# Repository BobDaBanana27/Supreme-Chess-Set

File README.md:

# Supreme Chess Set

> **Portable Magnetic Travel Chess Set**  
> Built for **Hack Club Half Life 2** | Repository: [`BobDaBanana27/Supreme-Chess-Set`](https://github.com/BobDaBanana27/Supreme-Chess-Set)  
> Total Bill of Materials: **$13.96 USD** (well within the $30.00 USD program budget)

---

## What is it?

The **Supreme Chess Set** is a compact, 3D-printed magnetic travel chess set designed to be taken anywhere. All 32 pieces have neodymium magnets pressed into their bases, and 64 matching magnets are embedded flush into the board squares beneath a thin plastic skin. This keeps pieces firmly in place during travel — the board can be tilted steeply or tossed in a bag without pieces sliding around.

When not in play, all 32 pieces store inside two slide-out trays built into the sides of the board chassis. The whole set closes into a flat clamshell that fits in a backpack pocket.

**Everything is 3D-printed on a standard FDM printer using PLA+ filament.**

---

## Features

- **Magnetic piece retention** — 5×2 mm N35 neodymium disc magnets in every piece base and board square. Pieces hold at up to ~80° tilt.
- **Slide-out storage trays** — both white and black armies have dedicated molded sockets so pieces snap in securely for travel. No rattling, no losing pieces.
- **Compact clamshell form factor** — 168 × 92 × 30 mm closed. Fits in a jacket pocket.
- **Full Staunton piece set** — all 6 piece types (King, Queen, Rook, Bishop, Knight, Pawn) modeled to standard proportions with a low center of gravity for stability.
- **Sub-$14 total cost** — only magnets, filament, and screws needed.
- **Fully open-source** — all CAD in FreeCAD 1.1 (`.FCStd` + `.step`).

---

## Bill of Materials

| # | Item | Qty | Unit Price | Total | Link |
|:---:|---|:---:|:---:|:---:|---|
| 1 | 5×2 mm N35 Neodymium Disc Magnets (pack of 100) | 96 | $0.035 | $3.36 | [AliExpress 100pcs 5×2mm N35](https://www.aliexpress.us/item/3256805987124930.html) / [Amazon](https://www.amazon.com/dp/B08V8MBRFL) |
| 2 | eSUN PLA+ Filament 1.75mm, 1kg spool (~220g used) | 0.22 kg | $18.00/kg | $3.96 | [Amazon eSUN PLA+ 1.75mm](https://www.amazon.com/dp/B07PGZNM34) |
| 3 | M2 × 8mm Socket Head Screws + Brass Heatsets (pack) | 8 | $0.08 | $0.64 | [AliExpress M2 Brass Heatsets & Screws](https://www.aliexpress.us/item/3256803248729112.html) |
| 4 | CA Super Glue (for magnet setting) | 1 | $6.00 | $6.00 | Any hardware store |
| **—** | **TOTAL** | | | **$13.96** | **Under the $30.00 cap** |

---

## 3D CAD Files

All parts designed in **FreeCAD 1.1** and exported as standard STEP files (importable in Fusion 360, Onshape, SolidWorks, etc.):

| Part | FreeCAD Source | STEP Export | Description |
|---|---|---|---|
| Base Chassis | [`cad/supreme_chess_base.FCStd`](cad/supreme_chess_base.FCStd) | [`cad/supreme_chess_base.step`](cad/supreme_chess_base.step) | Clamshell shell halves with slide-way rails and hinge knuckles |
| Board Grid Inlay | [`cad/board_grid_half.FCStd`](cad/board_grid_half.FCStd) | [`cad/board_grid_half.step`](cad/board_grid_half.step) | 8×8 grid with 32 blind magnet pockets (Ø5.2×2.2 mm) per half |
| Capture Tray | [`cad/capture_tray.FCStd`](cad/capture_tray.FCStd) | [`cad/capture_tray.step`](cad/capture_tray.step) | Slide-out drawer with 16 molded piece sockets (K, Q, R×2, B×2, N×2, P×8) |
| Chess Piece Set | [`cad/chess_pieces.FCStd`](cad/chess_pieces.FCStd) | [`cad/chess_pieces.step`](cad/chess_pieces.step) | All 6 Staunton piece types with magnet recess in base |

---

## Assembly Overview

1. **Print all parts** in PLA+ at 0.2mm layer height, 20% infill for the chassis and 40% for pieces.
2. **Press magnets** — use a dab of CA glue to set one N35 5×2mm magnet flush into each of the 32 board grid pockets, and one into each piece base. Keep polarity consistent across the board (all north-up), and all pieces opposite (south-up) so they attract.
3. **Insert heatsets** — press M2 brass threaded inserts into the hinge and latch points with a soldering iron.
4. **Assemble clamshell** — snap the board grid inlays into each chassis half, slide the capture trays in from the ends.
5. **Play.**

---

## Development Log 

<!-- Generated by Half Life from project w0snqy3nmk4d27srrj0r2tvn. Edits here are overwritten on the next sync. -->
<!-- Generated: 2026-11-09T02:09:53.469Z -->

> I am going to make a portable chess set that has magnets embedded in the pieces and board so the smaller-sized pieces won't fall off when you bump them.

| Week | Tier | Hours logged | Entries |
| --- | --- | --- | --- |
| Week 5 | Tier 1 | 12.5h | 1 |

## Contents

1. [2026-11-08: The first 2.5 hours consisted of brainstorming what I wanted to do, researching, and gathering the BOM. I decided to make a portable chess set with magnets embedded in the pieces and board so they don](#2026-11-08-the-first-25-hours-consisted-of-brainstorming-wha)

## Design

### 2026-11-08: The first 2.5 hours consisted of brainstorming what I wanted to do, researching, and gathering the BOM. I decided to make a portable chess set with magnets embedded in the pieces and board so they don

**12.5h**

The first 2.5 hours consisted of brainstorming what I wanted to do, researching, and gathering the BOM. I decided to make a portable chess set with magnets embedded in the pieces and board so they don't get knocked off. Since that doesn't seem like enough, I decided I should have a point counter that when a piece is captured, a sensor will trigger, and will change the score.(Requirements.md)

Hours 2.5-4 consisted of planning the bus and signal routing for the sensors. Resolved the microcontroller GPIO bottleneck: monitoring 30+ individual capture sockets with a 20-GPIO MCU required input multiplexing. Designed a cascaded 74HC165 8-bit parallel-in/serial-out (PISO) shift register architecture, chaining four ICs across a shared 3-wire synchronous bus (Latch, Clock, Serial Data). Also, defined the 32-bit hardware state word: bits 0–15 map to White's capture tray, and bits 16–31 map to Black's capture tray. Specified signal routing for the I2C OLED display, dual tactical navigation pushbuttons (Mode and Reset), and LiPo analog voltage divider. (Architecture.md)

Hour 4.5 consisted of having Ai help me calculate Magnetic Coupling Physics & Tolerance Analysis (I'm sorry the formula is outside of my expertise. haha).(Magnetic_Design.md):

Hour 4.5-6.5: Created the main electrical schematic and PCB in KiCad for the controller for the scoreboard thing and for the sensor strips. (supreme_chess.kicad_Sch, supreme_chess.kicad_PCB, Sensor_strip.kicad_sch, sensor_strip.kicad_pcb)

From hours 6.5-8 I built the folding base Chassis (cad/supreme_chess_base.FCStd), the board inlay grid (half a grid so 2x), the capture tray, and the pieces.

Hours 8-12.5 were the firmware side of things. I coded etc the the chess scoring system, sensors, the display Ui, power management, etc. (chess_engine.cpp and chess_engine.h, display_ui.cpp and display_ui.h, power_mgr.cpp and firmware/include/power_mgr.h, main.cpp, firmware/platformio.ini, and supreme_chess_firmware.ino)

Full documentation in [`docs/`](docs/).

---

## License

MIT — free and open for educational and maker use. Built for **Hack Club Half Life 2**.

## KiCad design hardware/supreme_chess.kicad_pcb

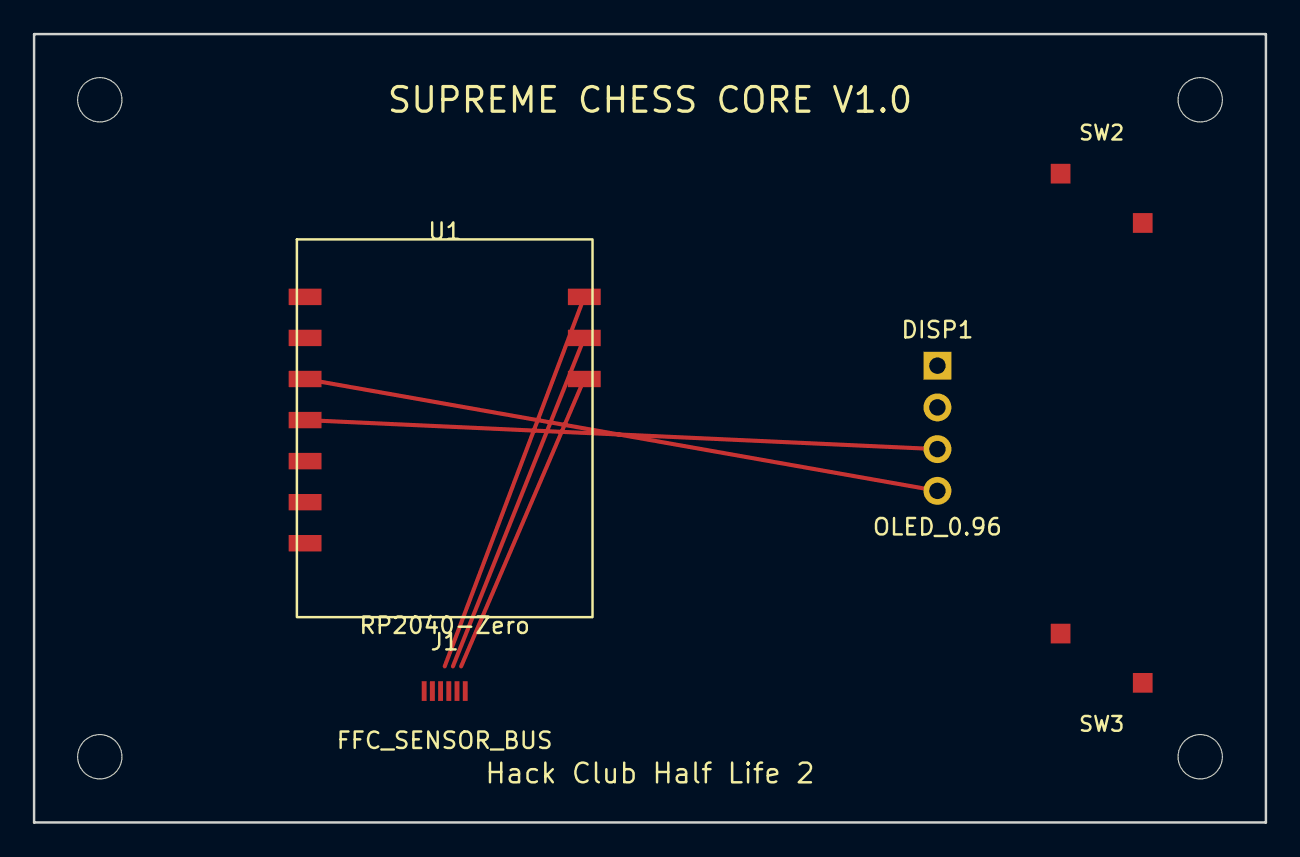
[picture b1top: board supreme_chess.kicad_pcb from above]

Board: 2 copper layers, 75.0 x 48.0 mm, 5 parts (0 on the bottom side), 7 nets.

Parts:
DISP1: OLED_0.96; PinHeader_1x04_P2.54mm_Vertical
J1: FFC_SENSOR_BUS; Hirose_FH12-6S-0.5SH
SW2, SW3: SW_Push_1P1T_NO_6x6mm
U1: RP2040-Zero

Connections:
+3V3: DISP1.2, J1.2, U1.2
GND: DISP1.1, J1.1, J1.6, SW2.1, SW3.1, U1.1
SCL: DISP1.3, U1.4
SDA: DISP1.4, U1.3
SR_CLK: J1.4, U1.9
SR_DATA: J1.5, U1.10
SR_LOAD: J1.3, U1.8

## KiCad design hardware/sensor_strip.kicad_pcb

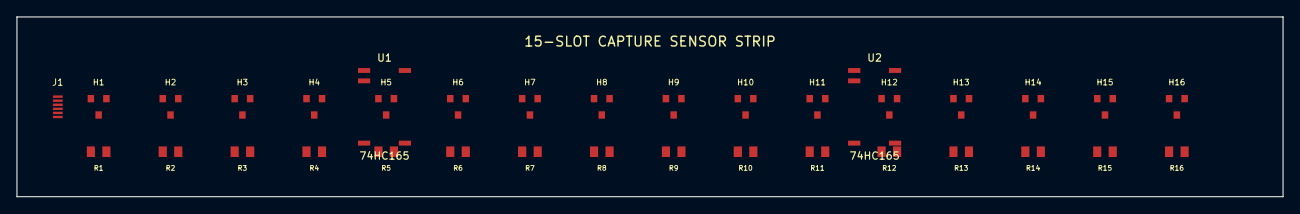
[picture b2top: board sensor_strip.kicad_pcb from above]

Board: 2 copper layers, 155.0 x 22.0 mm, 35 parts (0 on the bottom side), 5 nets, no tracks yet.

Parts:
H1, H2, H3, H4, H5, H6, H7, H8, H9, H10, H11, H12, H13, H14, H15, H16: SOT-23
J1: Hirose_FH12-6S-0.5SH
R1, R2, R3, R4, R5, R6, R7, R8, R9, R10, R11, R12, R13, R14, R15, R16: R_0805_2012Metric
U1, U2: 74HC165; SOIC-16_3.9x9.9mm_P1.27mm

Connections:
+3V3: H1.1, H2.1, H3.1, H4.1, H5.1, H6.1, H7.1, H8.1, H9.1, H10.1, H11.1, H12.1, H13.1, H14.1, H15.1, H16.1, J1.2, R1.1, R2.1, R3.1, R4.1, R5.1, R6.1, R7.1, R8.1, R9.1, R10.1, R11.1, R12.1, R13.1, R14.1, R15.1, R16.1, U1.16, U2.16
GND: H1.2, H2.2, H3.2, H4.2, H5.2, H6.2, H7.2, H8.2, H9.2, H10.2, H11.2, H12.2, H13.2, H14.2, H15.2, H16.2, J1.1, J1.6, U1.8, U2.8
SR_CLK: J1.4, U1.2, U2.2
SR_DATA: J1.5, U1.9
SR_LOAD: J1.3, U1.1, U2.1

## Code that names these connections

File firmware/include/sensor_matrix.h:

#pragma once

#include <stdint.h>
#include <stdbool.h>

#ifdef __cplusplus
extern "C" {
#endif

// Hardware Pin Assignments for RP2040-Zero
#define PIN_SR_LOAD       10  // GPIO 10: 74HC165 Parallel Load (/PL) - Active LOW
#define PIN_SR_CLK        11  // GPIO 11: 74HC165 Shift Clock (CP)
#define PIN_SR_DATA       12  // GPIO 12: 74HC165 Serial Data Input (Q7)
#define PIN_TRAY_W_EN     0   // GPIO 0: White Tray Enable (Active LOW)
#define PIN_TRAY_B_EN     1   // GPIO 1: Black Tray Enable (Active LOW)

#define TOTAL_SLOTS       32  // 16 White slots + 16 Black slots (Full 32-piece set storage)
#define DEBOUNCE_SAMPLES  3   // Number of consecutive matching reads required

// Bitfield definitions (Exact 32-bit mapping for 4x 74HC165 8-bit registers):
// White Tray (16 Bits):
//   Row 1: Bits 0-7: White Pawns 1-8 (1 pt each, pitch 18.0mm, Ø13.0mm)
//   Row 2: Organized Major & Royal Rank (pitch 18.0mm, Left-to-Right):
//     Bit 8:  White King (0 pts / Resignation trigger & Travel Home, Ø15.5mm)
//     Bit 9:  White Queen (9 pts, Ø15.5mm)
//     Bit 10: White Rook 1 (5 pts, Ø14.0mm)
//     Bit 11: White Rook 2 (5 pts, Ø14.0mm)
//     Bit 12: White Knight 1 (3 pts, Ø14.0mm)
//     Bit 13: White Knight 2 (3 pts, Ø14.0mm)
//     Bit 14: White Bishop 1 (3 pts, Ø14.0mm)
//     Bit 15: White Bishop 2 (3 pts, Ø14.0mm)
// Black Tray (16 Bits):
//   Row 1: Bits 16-23: Black Pawns 1-8 (1 pt each, pitch 18.0mm, Ø13.0mm)
//   Row 2: Organized Major & Royal Rank (pitch 18.0mm, Left-to-Right):
//     Bit 24: Black King (0 pts / Resignation trigger & Travel Home, Ø15.5mm)
//     Bit 25: Black Queen (9 pts, Ø15.5mm)
//     Bit 26: Black Rook 1 (5 pts, Ø14.0mm)
//     Bit 27: Black Rook 2 (5 pts, Ø14.0mm)
//     Bit 28: Black Knight 1 (3 pts, Ø14.0mm)
//     Bit 29: Black Knight 2 (3 pts, Ø14.0mm)
//     Bit 30: Black Bishop 1 (3 pts, Ø14.0mm)
//     Bit 31: Black Bishop 2 (3 pts, Ø14.0mm)

typedef struct {
    uint32_t raw_state;        // Current raw un-debounced reading
    uint32_t debounced_state;  // Stable filtered bitfield
    uint32_t changed_mask;     // Bits that changed since last update
    uint8_t  history_index;
    uint32_t history[DEBOUNCE_SAMPLES];
} SensorMatrix_t;

void SensorMatrix_Init(SensorMatrix_t *sm);
bool SensorMatrix_Scan(SensorMatrix_t *sm);
bool SensorMatrix_IsPiecePresent(const SensorMatrix_t *sm, uint8_t slot_index);
uint32_t SensorMatrix_GetWhiteBitfield(const SensorMatrix_t *sm);
uint32_t SensorMatrix_GetBlackBitfield(const SensorMatrix_t *sm);

#ifdef __cplusplus
}
#endif
